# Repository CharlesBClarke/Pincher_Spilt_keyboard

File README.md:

# Pincher\_Split\_keyboard (WIP)

The **Pincher Split Keyboard** is a work-in-progress split mechanical keyboard with the thumb cluster positioned underneath the main keys.

The design philosophy is based on the natural motion of the human thumb — it's more comfortable for thumbs to pinch toward the fingers rather than push forward in the same direction as the fingers.

---

## Features

- Split ergonomic layout (3 rows × 5 columns per side)
- Underslung thumb clusters
- Compact and minimalistic
- No diode soldering required

## Design Goals

- Improve thumb ergonomics
- Encourage more natural hand positioning

## Status

- PCB design: In progress
- Case design: In progress
- Firmware: TBD

## Images

## Build Instructions

*(Coming soon)*

## Future Plans

- Finalize and test PCB prototype
- Design and 3D print a matching case
- Develop QMK/VIAL firmware support
- Explore hotswap socket compatibility
- Create assembly guide and documentation
- Make board more compact for travel.
- Support ULP if possible

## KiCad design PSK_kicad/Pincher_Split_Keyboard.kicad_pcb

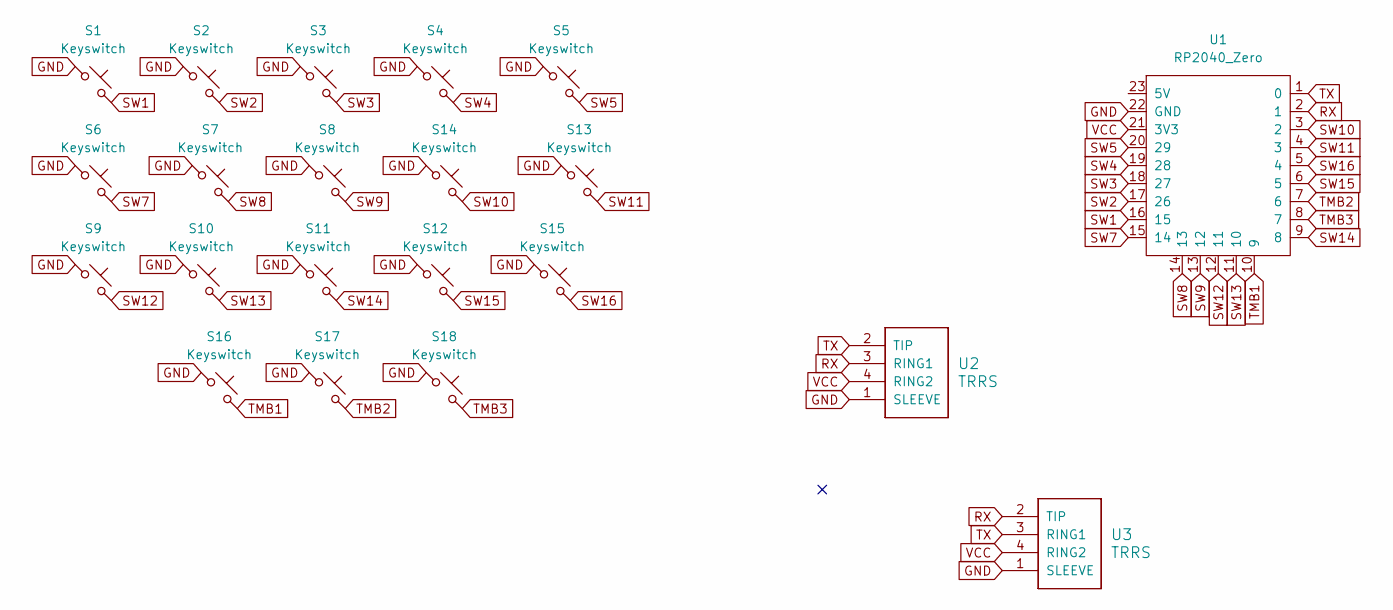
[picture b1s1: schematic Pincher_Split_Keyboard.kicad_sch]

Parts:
S1, S2, S3, S4, S5, S6, S7, S8, S9, S10, S11, S12, S13, S14, S15, S16, S17, S18: Keyswitch; Choc_V1_rev_test_no_bounds
U1: RP2040_Zero
U2, U3: TRRS; Jack_3.5mm_PJ320D_Horizontal

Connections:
GND: S1.1, S2.1, S3.1, S4.1, S5.1, S6.1, S7.1, S8.1, S9.1, S10.1, S11.1, S12.1, S13.1, S14.1, S15.1, S16.1, S17.1, S18.1, U1.22 (GND), U2.1 (SLEEVE), U3.1 (SLEEVE)
RX: U1.2 (1), U2.3 (RING1), U3.2 (TIP)
SW1: S1.2, U1.16 (15)
SW2: S2.2, U1.17 (26)
SW3: S3.2, U1.18 (27)
SW4: S4.2, U1.19 (28)
SW5: S5.2, U1.20 (29)
SW7: S6.2, U1.15 (14)
SW8: S7.2, U1.14 (13)
SW9: S8.2, U1.13 (12)
SW10: S14.2, U1.3 (2)
SW11: S13.2, U1.4 (3)
SW12: S9.2, U1.12 (11)
SW13: S10.2, U1.11 (10)
SW14: S11.2, U1.9 (8)
SW15: S12.2, U1.6 (5)
SW16: S15.2, U1.5 (4)
TMB1: S16.2, U1.10 (9)
TMB2: S17.2, U1.7 (6)
TMB3: S18.2, U1.8 (7)
TX: U1.1 (0), U2.2 (TIP), U3.3 (RING1)
VCC: U1.21 (3V3), U2.4 (RING2), U3.4 (RING2)

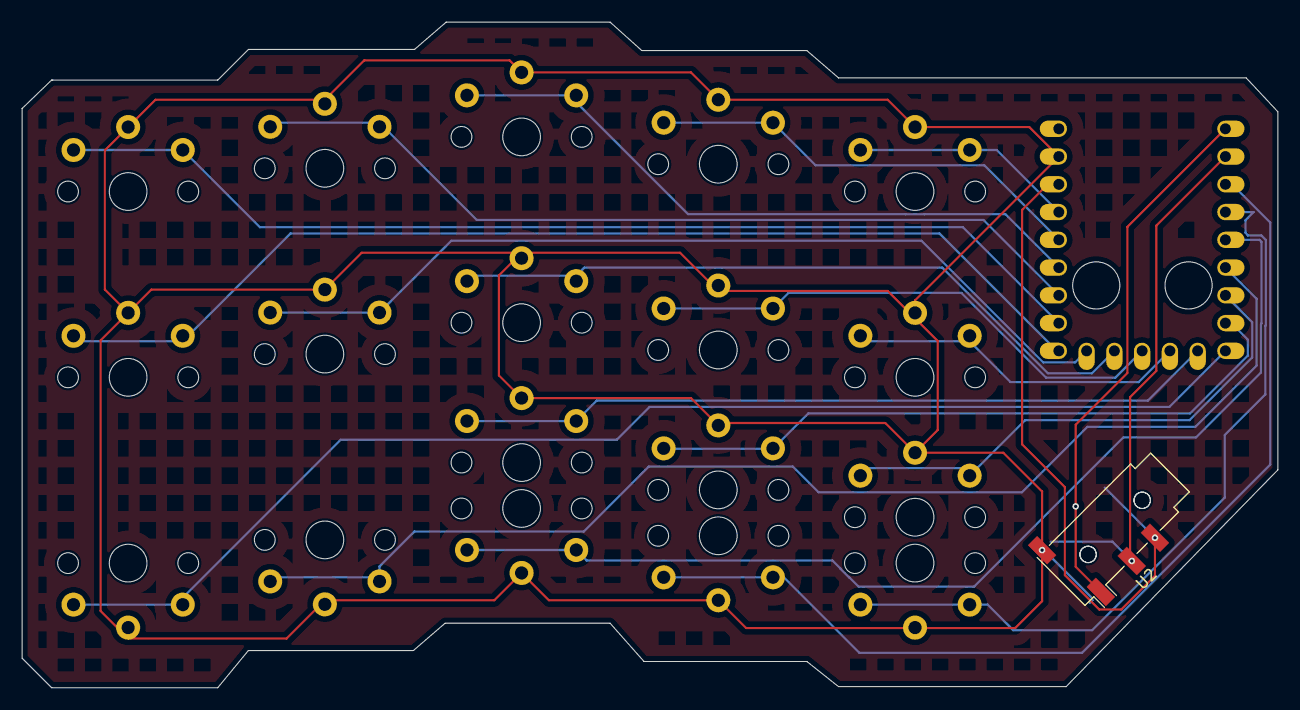
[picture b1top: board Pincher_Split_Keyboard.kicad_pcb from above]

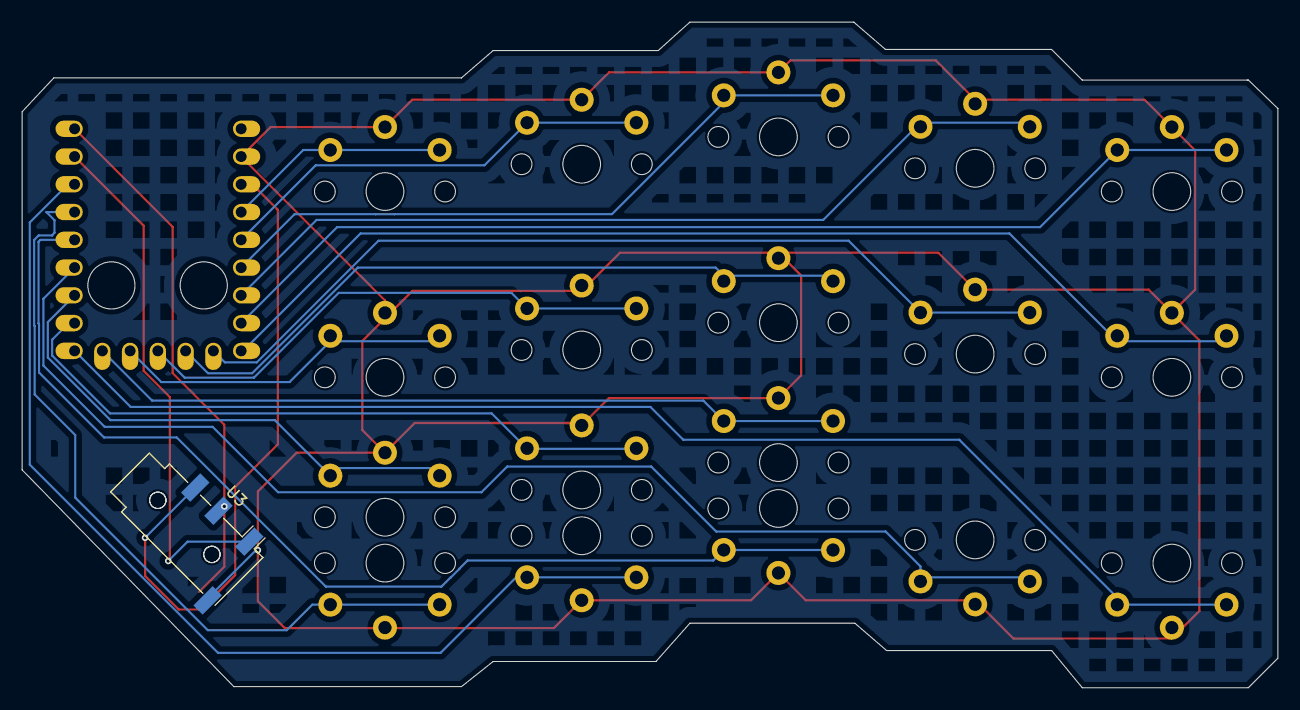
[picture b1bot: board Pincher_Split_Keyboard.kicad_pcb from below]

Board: 2 copper layers, 114.9 x 60.9 mm, 21 parts (4 on the bottom side), 22 nets.

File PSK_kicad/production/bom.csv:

Designator,Footprint,Quantity,Value,LCSC Part #
"S1, S10, S11, S12, S13, S14, S15, S16, S17, S18, S2, S3, S4, S5, S6, S7, S8, S9",Choc_V1_rev_test_no_bounds,18,Keyswitch,
U1,RP2040_Zero,1,RP2040_Zero,
"U2, U3",Jack_3.5mm_PJ320D_Horizontal,2,TRRS,

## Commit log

2025-04-28 Hello World
2025-04-28 added case model
2025-04-28 added ReadMe
2025-04-28 revised readme
2025-04-28 imported 3D models
2025-04-28 images
2025-04-28 readme again
2025-04-28 making mess
2025-05-01 fixed rx tx
2025-05-01 added front plate
2025-05-01 updated git ignore
2025-05-01 removed untracked
2025-05-01 better front plate
2025-05-01 new render
2025-05-01 Create LICENSE
2025-05-01 I don't know
2025-05-01 removed production
2025-05-01 add stuff
2025-05-01 amended readme
